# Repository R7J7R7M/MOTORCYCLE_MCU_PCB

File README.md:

# MOTORCYCLE_MCU_PCB
This project contains the PCB design of the motorcycle device
# 🚲 Beyond the Basics: Upgrading to a Smart Bicycle

## 🔥 Introduction

This project aims to transform a normal bicycle into a smart one by integrating GSM, OLED display, and various other market-available technologies. The goal is to enhance functionality and convenience, making the bicycle smarter and more efficient. (Refer to the Features section for a detailed description.)

## ⚡ Features

- 💡 Control of lights (front/rear indicators, headlight) with 7 output connectors
- 📟 Accelerometer sensor interface
- 📶 Bluetooth HM-10 interface
- 🔄 EN and Reset pinout for efficient programming and debugging
- 🔵 Power-on LED indicator
- 🛰️ SIM800C GPS module interface
- 🔋 Operates on a 12V battery
- 🔌 Interface for current sensor, fuel sensor, tilt sensor, and programming pins
- 📺 OLED display interface (without buttons)
- 🧠 **Brain**: ESP32

## 🛠️ Software & External Libraries

1. **KiCAD Version 8.0**
2. **External Libraries**: Refer to the external library section for details on the libraries used, mostly sourced from Ultra Librarian.

## 🏗️ Fabrication

> **⚠️ Note:** This design has **not been fabricated** yet. If you plan to fabricate it, ensure a thorough schematic and layout check before proceeding.

## 🛑 Known Issues

1. ⚙️ The relay footprint used is for an expensive relay. If you are looking for a budget-friendly alternative, consider replacing it with a cheaper option.

## 📩 Contact

**👤 Name:** Gokul Rajaram\
**📧 Email:** [gokulrajarama@gmail.com](mailto\:gokulrajarama@gmail.com)\
**📞 Contact:** +91 9025938754

##

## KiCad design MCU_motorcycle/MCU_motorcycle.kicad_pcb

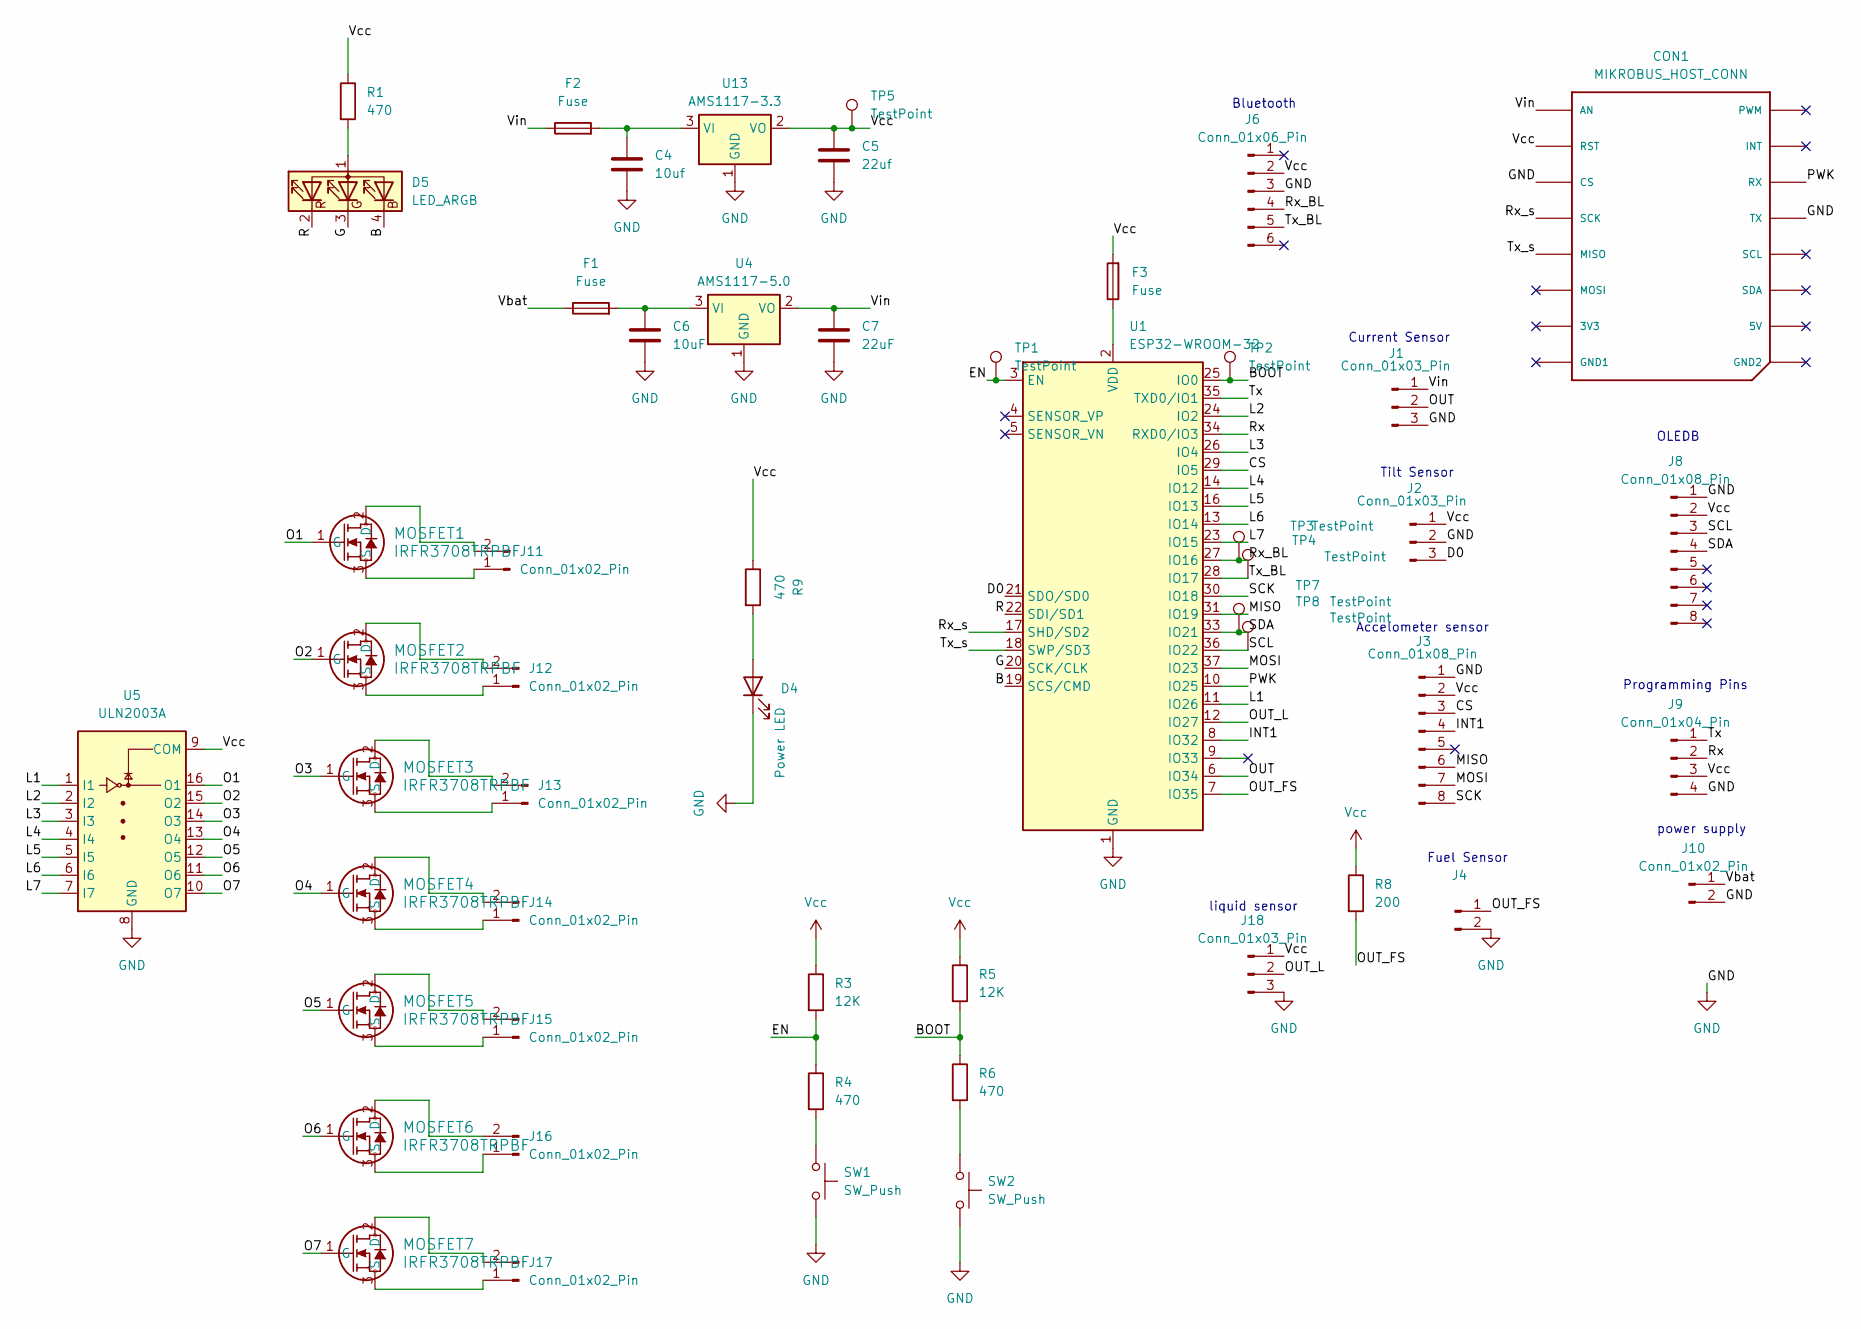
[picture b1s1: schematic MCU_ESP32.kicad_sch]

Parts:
C4: 10uf; C_0603_1608Metric_Pad1.08x0.95mm_HandSolder
C5: 22uf; C_0603_1608Metric_Pad1.08x0.95mm_HandSolder
C6: 10uF; C_0603_1608Metric_Pad1.08x0.95mm_HandSolder
C7: 22uF; C_0603_1608Metric_Pad1.08x0.95mm_HandSolder
CON1: MIKROBUS_HOST_CONN
D4: Power LED; LED_0603_1608Metric_Pad1.05x0.95mm_HandSolder
D5: LED_ARGB; LED_AAA3528LSEKJ3ZGKQBKS
F1, F2, F3: Fuse; Fuse_1206_3216Metric_Pad1.42x1.75mm_HandSolder
J1, J18: Conn_01x03_Pin; PinSocket_1x03_P2.54mm_Vertical
J2: Conn_01x03_Pin; PinSocket_1x03_P2.54mm_Horizontal
J3, J8: Conn_01x08_Pin; PinSocket_1x08_P2.54mm_Vertical
J4: Conn_01x02_Pin; PinSocket_1x02_P2.54mm_Vertical
J6: Conn_01x06_Pin; PinSocket_1x06_P2.54mm_Horizontal
J9: Conn_01x04_Pin; PinSocket_1x04_P2.54mm_Vertical
J10, J11, J12, J13, J14, J15, J16, J17: Conn_01x02_Pin; TE_282837-2
MOSFET1, MOSFET2, MOSFET3, MOSFET4, MOSFET5, MOSFET6, MOSFET7: IRFR3708TRPBF; DPAK_TO-236AA_INF
R1, R4, R6, R9: 470; R_0805_2012Metric_Pad1.20x1.40mm_HandSolder
R3, R5: 12K; R_0805_2012Metric_Pad1.20x1.40mm_HandSolder
R8: 200; R_0805_2012Metric_Pad1.20x1.40mm_HandSolder
SW1, SW2: SW_Push; SW_Push_1P1T_NO_6x6mm_H9.5mm
TP1, TP2, TP3, TP4, TP5, TP7, TP8: TestPoint; TestPoint_Pad_1.5x1.5mm
U1: ESP32-WROOM-32
U4: AMS1117-5.0; SOT-223-3_TabPin2
U5: ULN2003A; DIP762W46P254L1969H533Q16
U13: AMS1117-3.3; SOT-223-3_TabPin2

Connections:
/MCU_ESP32/B: D5.4 (BK), U1.19 (SCS/CMD)
/MCU_ESP32/BOOT: R5.2, R6.1, TP2.1, U1.25 (IO0)
/MCU_ESP32/CS: J3.3, U1.29 (IO5)
/MCU_ESP32/D0: J2.3, U1.21 (SDO/SD0)
/MCU_ESP32/EN: R3.2, R4.1, TP1.1, U1.3 (EN)
/MCU_ESP32/G: D5.3 (GK), U1.20 (SCK/CLK)
/MCU_ESP32/INT1: J3.4, U1.8 (IO32)
/MCU_ESP32/L1: U1.11 (IO26), U5.1 (I1)
/MCU_ESP32/L2: U1.24 (IO2), U5.2 (I2)
/MCU_ESP32/L3: U1.26 (IO4), U5.3 (I3)
/MCU_ESP32/L4: U1.14 (IO12), U5.4 (I4)
/MCU_ESP32/L5: U1.16 (IO13), U5.5 (I5)
/MCU_ESP32/L6: U1.13 (IO14), U5.6 (I6)
/MCU_ESP32/L7: U1.23 (IO15), U5.7 (I7)
/MCU_ESP32/MISO: J3.6, U1.31 (IO19)
/MCU_ESP32/MOSI: J3.7, U1.37 (IO23)
/MCU_ESP32/O1: MOSFET1.1 (G), U5.16 (O1)
/MCU_ESP32/O2: MOSFET2.1 (G), U5.15 (O2)
/MCU_ESP32/O3: MOSFET3.1 (G), U5.14 (O3)
/MCU_ESP32/O4: MOSFET4.1 (G), U5.13 (O4)
/MCU_ESP32/O5: MOSFET5.1 (G), U5.12 (O5)
/MCU_ESP32/O6: MOSFET6.1 (G), U5.11 (O6)
/MCU_ESP32/O7: MOSFET7.1 (G), U5.10 (O7)
/MCU_ESP32/OUT: J1.2, U1.6 (IO34)
/MCU_ESP32/OUT_FS: J4.1, R8.2, U1.7 (IO35)
/MCU_ESP32/OUT_L: J18.2, U1.12 (IO27)
/MCU_ESP32/PWK: CON1.P14 (RX), U1.10 (IO25)
/MCU_ESP32/R: D5.2 (RK), U1.22 (SDI/SD1)
/MCU_ESP32/Rx: J9.2, U1.34 (RXD0/IO3)
/MCU_ESP32/Rx_BL: J6.4, TP3.1, U1.27 (IO16)
/MCU_ESP32/Rx_s: CON1.P4 (SCK), U1.17 (SHD/SD2)
/MCU_ESP32/SCK: J3.8, U1.30 (IO18)
/MCU_ESP32/SCL: J8.3, TP8.1, U1.36 (IO22)
/MCU_ESP32/SDA: J8.4, TP7.1, U1.33 (IO21)
/MCU_ESP32/Tx: J9.1, U1.35 (TXD0/IO1)
/MCU_ESP32/Tx_BL: J6.5, TP4.1, U1.28 (IO17)
/MCU_ESP32/Tx_s: CON1.P5 (MISO), U1.18 (SWP/SD3)
/MCU_ESP32/Vbat: F1.1, J10.1
/MCU_ESP32/Vin: C7.1, CON1.P1 (AN), F2.1, J1.1, U4.2 (VO)
GND: C4.2, C5.2, C6.2, C7.2, CON1.P3 (CS), CON1.P13 (TX), D4.1 (K), J1.3, J2.2, J3.1, J4.2, J6.3, J8.1, J9.4, J10.2, J18.3, SW1.2, SW2.2, U1.1 (GND), U1.15 (GND), U1.38 (GND), U1.39 (GND), U4.1 (GND), U5.8 (GND), U13.1 (GND)
unnamed: D4.2 (A), R9.2
unnamed: D5.1 (A), R1.2
unnamed: J11.1, MOSFET1.3 (S)
unnamed: J11.2, MOSFET1.2 (D)
unnamed: J12.1, MOSFET2.3 (S)
unnamed: J12.2, MOSFET2.2 (D)
unnamed: J13.1, MOSFET3.3 (S)
unnamed: J13.2, MOSFET3.2 (D)
unnamed: J14.1, MOSFET4.3 (S)
unnamed: J14.2, MOSFET4.2 (D)
unnamed: J15.1, MOSFET5.3 (S)
unnamed: J15.2, MOSFET5.2 (D)
unnamed: J16.1, MOSFET6.3 (S)
unnamed: J16.2, MOSFET6.2 (D)
unnamed: J17.1, MOSFET7.3 (S)
unnamed: J17.2, MOSFET7.2 (D)
unnamed: R4.2, SW1.1
unnamed: R6.2, SW2.1
unnamed: F3.1, U1.2 (VDD)
unnamed: C6.1, F1.2, U4.3 (VI)
unnamed: C4.1, F2.2, U13.3 (VI)
Vcc: C5.1, CON1.P2 (RST), F3.2, J2.1, J3.2, J6.2, J8.2, J9.3, J18.1, R1.1, R3.1, R5.1, R8.1, R9.1, TP5.1, U5.9 (COM), U13.2 (VO)

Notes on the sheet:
Bluetooth
Tilt Sensor
Current Sensor
liquid sensor
Accelometer sensor
power supply
Fuel Sensor
Programming Pins
OLEDB

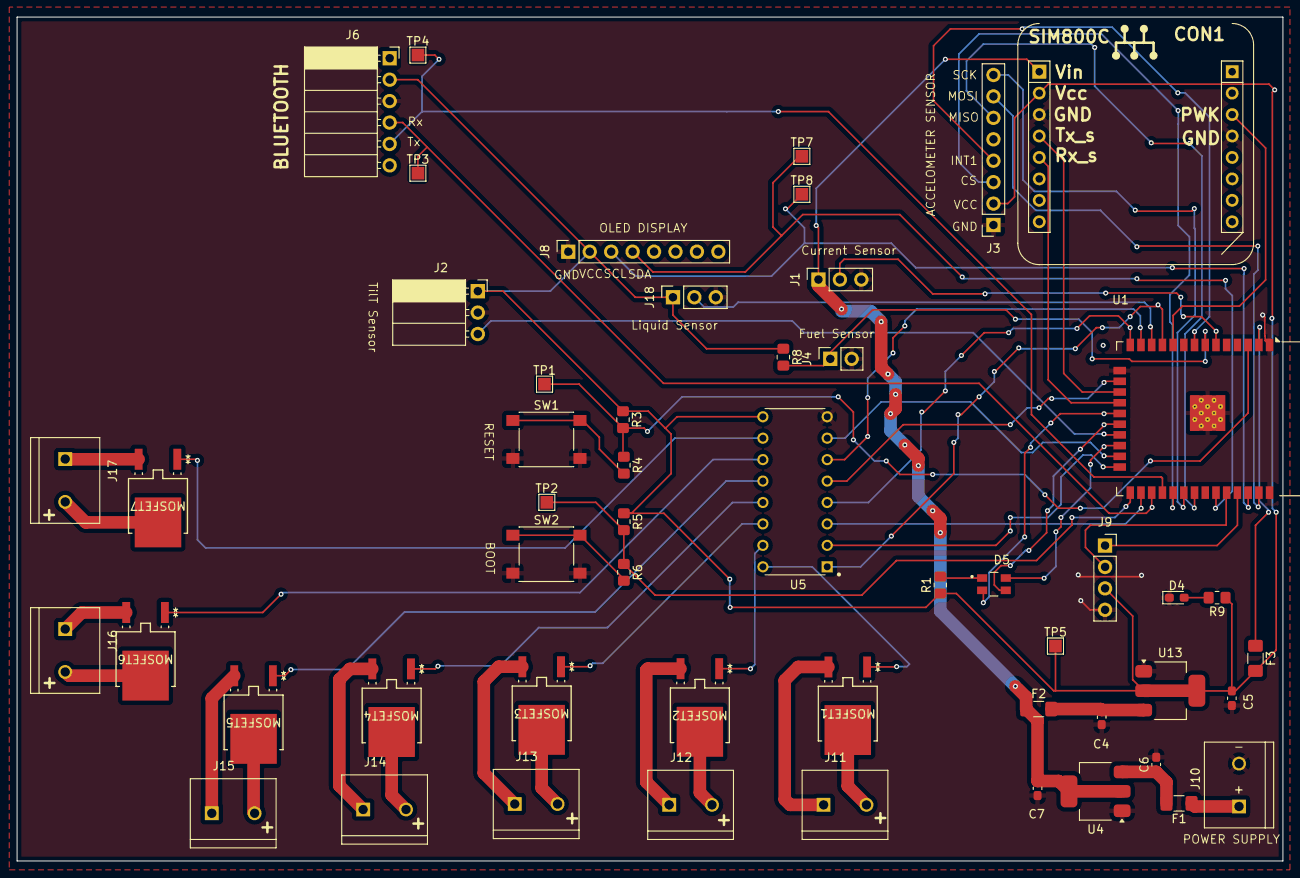
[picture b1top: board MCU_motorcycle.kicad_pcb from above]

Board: 2 copper layers, 150.0 x 100.0 mm, 53 parts (0 on the bottom side), 62 nets.

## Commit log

2025-04-03 Update README.md
    added image
